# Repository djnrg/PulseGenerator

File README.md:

PulseGenerator
==============

Pulse Generator base on Arduino.

Change static voltage (max. 24V) to PWM. 

In this evolution we may setup frequency [1-500] and Duty Cycle [0-99].

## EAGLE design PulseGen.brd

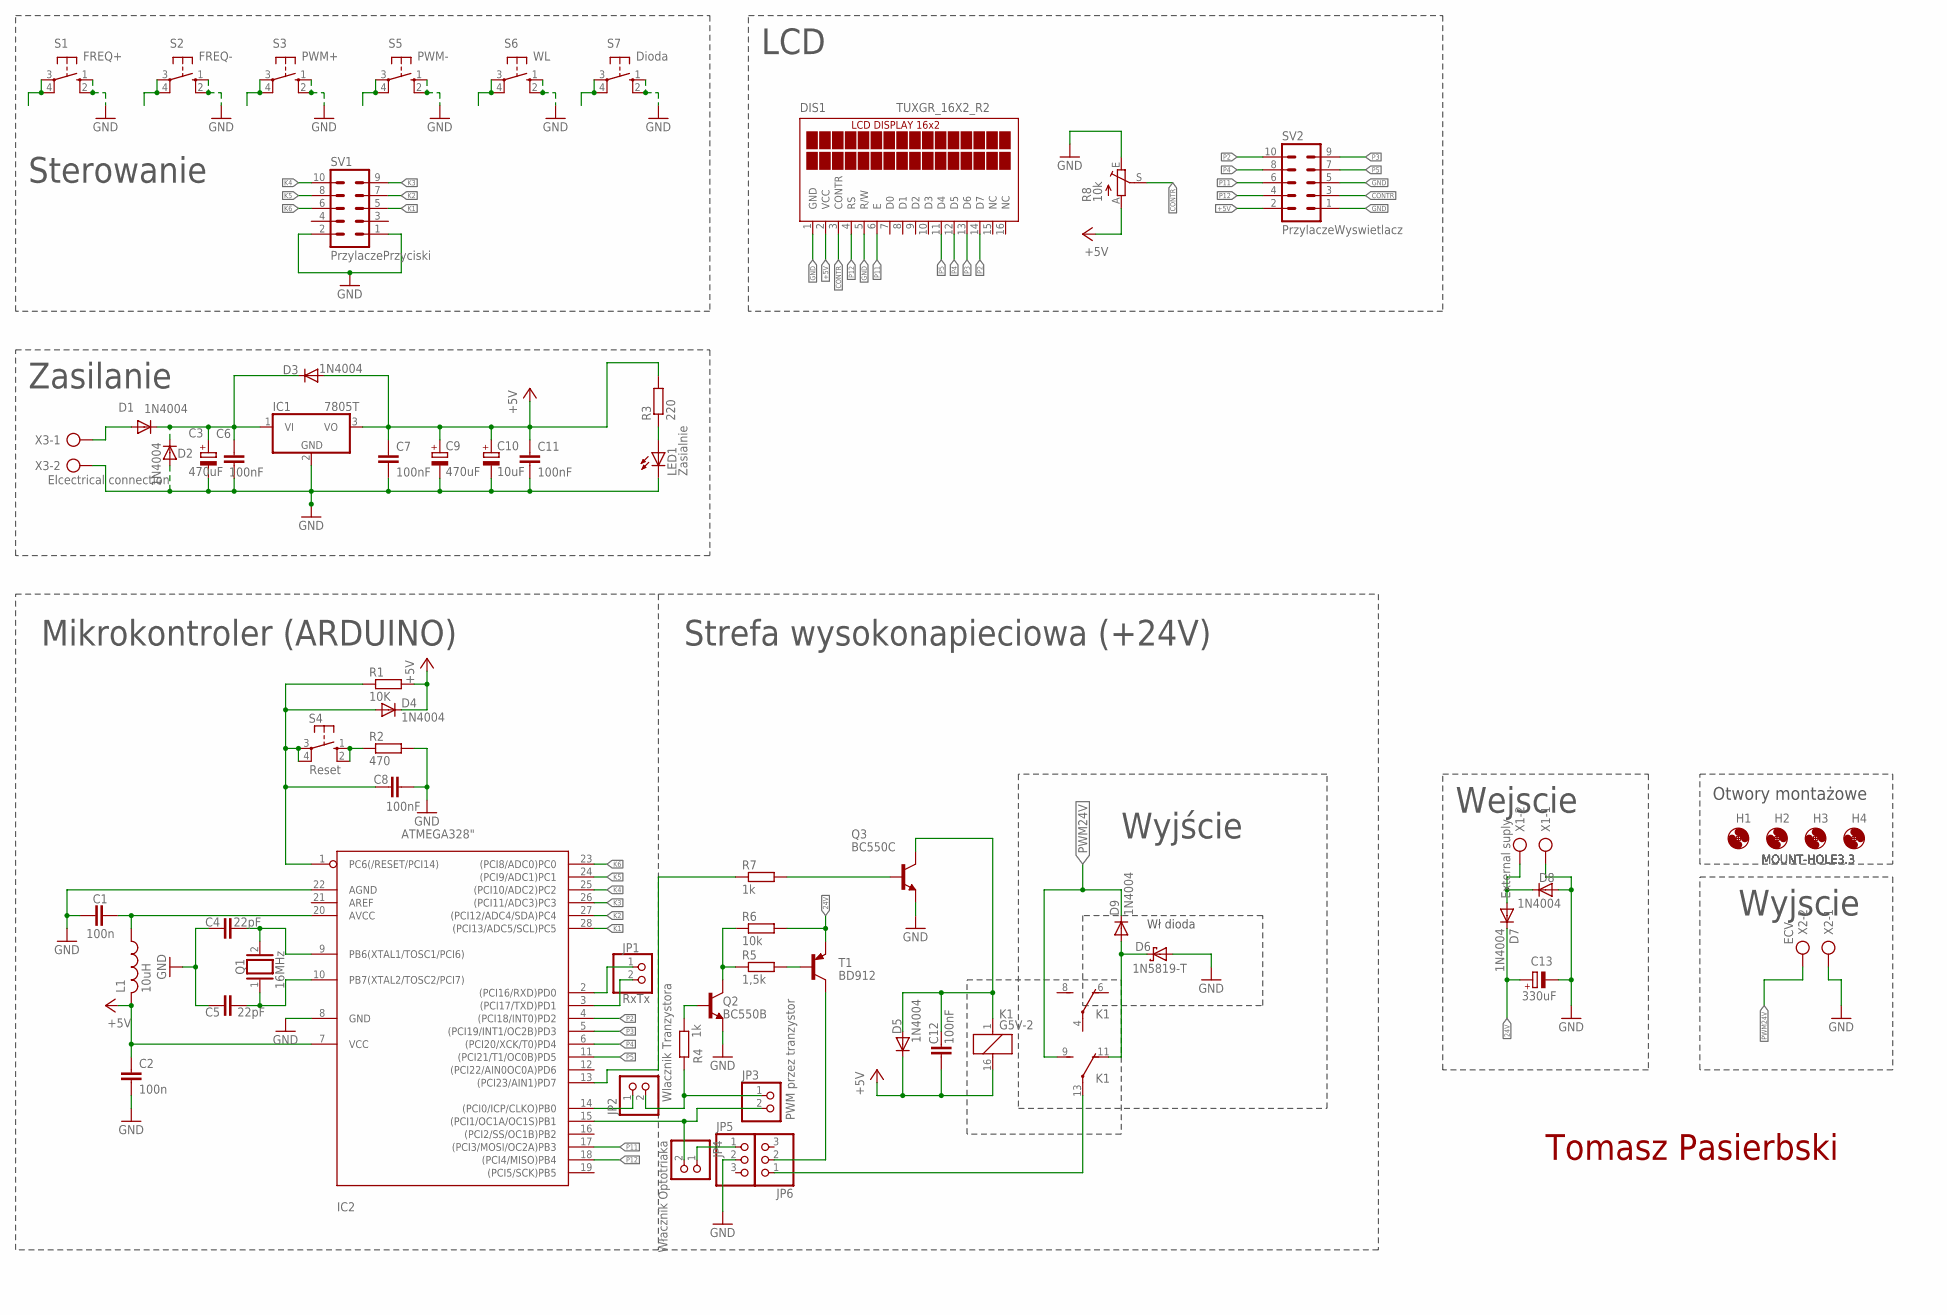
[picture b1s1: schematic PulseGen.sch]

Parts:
C1, C2: 100n; C025-030X050
C3, C9: 470uF; E3,5-8
C4, C5: 22pF; C025-024X044
C6, C7, C8, C11, C12: 100nF; C025-030X050
C10: 10uF; E5-6
C13: 330uF; E7,5-18
D1, D2, D3, D4, D5, D7, D8, D9: 1N4004; DO41-10
D6: 1N5819-T; DO41-7.6
DIS1: TUXGR_16X2_R2
H1, H2, H3, H4: MOUNT-HOLE3.3; 3,3
IC1: 7805T; TO220H
IC2: ATMEGA328"; ATMEGA328
JP1: RxTx; 1X02
JP2: Wlacznik Tranzystora; 1X02
JP3: PWM przez tranzystor; 1X02
JP4: Włacznik Optotriaka; 1X02
JP5, JP6: PINHD-1X3; 1X03
K1: G5V-2
L1: 10uH; 0204/7
LED1: Zasialnie; LED5MM
Q1: 16MHz; QS
Q2: BC550B; TO92-EBC
Q3: BC550C; TO92-EBC
R1: 10K; 0207/2V
R2: 470; 0207/2V
R3: 220; 0204/7
R4, R7: 1k; 0204/7
R5: 1,5k; 0207/12
R6: 10k; 0204/7
R8: 10k; CA6V
S1: FREQ+; B3F-10XX
S2: FREQ-; B3F-10XX
S3: PWM+; B3F-10XX
S4: Reset; B3F-10XX
S5: PWM-; B3F-10XX
S6: WL; B3F-10XX
S7: Dioda; B3F-10XX
SV1: PrzylaczePrzyciski; ML10
SV2: PrzylaczeWyswietlacz; ML10
T1: BD912; TO220
X1: External suply; AK300/2
X2: ECV; AK300/2
X3: Elcectrical connection; AK300/2

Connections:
24V: C13.+, D7.C, R6.2, T1.3 (E)
+5V: C2.1, C7.1, C9.+, C10.+, C11.1, C12.2, D3.A, D4.C, D5.C, DIS1.2 (VCC), IC1.3 (VO), IC2.7 (VCC), K1.16 (2), L1.2, R1.2, R3.2, R8.A, SV2.2
+24V: D7.A, D8.C, X1.2
CONTR: DIS1.3 (CONTR), R8.S, SV2.3
GND: C1.2, C2.2, C3.-, C4.1, C5.1, C6.2, C7.2, C8.2, C9.-, C10.-, C11.2, C13.-, D2.A, D6.A, D8.A, DIS1.1 (GND), DIS1.5 (R/W), IC1.2 (GND), IC2.8 (GND), IC2.22 (AGND), JP5.2, LED1.K (C), Q2.E, Q3.E, R2.2, R8.E, S1.1 (S), S1.2 (S1), S2.1 (S), S2.2 (S1), S3.1 (S), S3.2 (S1), S5.1 (S), S5.2 (S1), S6.1 (S), S6.2 (S1), S7.1 (S), S7.2 (S1), SV1.1, SV1.2, SV2.1, SV2.5, X1.1, X2.1, X3.2
K1: IC2.28 ((PCI13/ADC5/SCL)PC5), SV1.5
K2: IC2.27 ((PCI12/ADC4/SDA)PC4), SV1.7
K3: IC2.26 ((PCI11/ADC3)PC3), SV1.9
K4: IC2.25 ((PCI10/ADC2)PC2), SV1.10
K5: IC2.24 ((PCI9/ADC1)PC1), SV1.8
K6: IC2.23 ((PCI8/ADC0)PC0), SV1.6
unnamed: C5.2, IC2.10 (PB7(XTAL2/TOSC2/PCI7)), Q1.1
unnamed: C3.+, C6.1, D1.C, D2.C, D3.C, IC1.1 (VI)
unnamed: C4.2, IC2.9 (PB6(XTAL1/TOSC1/PCI6)), Q1.2
unnamed: D1.A, X3.1
unnamed: C12.1, D5.A, K1.1, Q3.C
unnamed: C1.1, IC2.20 (AVCC), L1.1
unnamed: Q3.B, R7.2
unnamed: JP2.2, JP3.1, R4.1
unnamed: Q2.C, R5.1, R6.1
unnamed: R2.1, S4.1 (S), S4.2 (S1)
unnamed: C8.1, D4.A, IC2.1 (PC6(/RESET/PCI14)), R1.1, S4.3, S4.4 (P1)
unnamed: JP6.1, K1.13
unnamed: IC2.13 ((PCI23/AIN1)PD7), R7.1
unnamed: Q2.B, R4.2
unnamed: R5.2, T1.1 (B)
unnamed: JP6.2, T1.2 (C)
unnamed: IC2.14 ((PCI0/ICP/CLKO)PB0), JP2.1
unnamed: LED1.A, R3.1
unnamed: IC2.15 ((PCI1/OC1A/OC1S)PB1), JP3.2, JP4.2
unnamed: S1.3, S1.4 (P1)
unnamed: S2.3, S2.4 (P1)
unnamed: S3.3, S3.4 (P1)
unnamed: S5.3, S5.4 (P1)
unnamed: S6.3, S6.4 (P1)
unnamed: S7.3, S7.4 (P1)
unnamed: IC2.3 ((PCI17/TXD)PD1), JP1.2
unnamed: IC2.2 ((PCI16/RXD)PD0), JP1.1
unnamed: JP4.1, JP5.1
unnamed: D6.C, D9.A, K1.11 (O)
P2: DIS1.14 (D7), IC2.4 ((PCI18/INT0)PD2), SV2.10
P3: DIS1.13 (D6), IC2.5 ((PCI19/INT1/OC2B)PD3), SV2.9
P4: DIS1.12 (D5), IC2.6 ((PCI20/XCK/T0)PD4), SV2.8
P5: DIS1.11 (D4), IC2.11 ((PCI21/T1/OC0B)PD5), SV2.7
P11: DIS1.6 (E), IC2.17 ((PCI3/MOSI/OC2A)PB3), SV2.6
P12: DIS1.4 (RS), IC2.18 ((PCI4/MISO)PB4), SV2.4
PWM24V: D9.C, K1.9 (S), X2.2

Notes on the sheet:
Zasilanie
LCD
Wejscie
Wyjscie
Sterowanie
Wł dioda
Wyjście
Mikrokontroler (ARDUINO)
Strefa wysokonapieciowa (+24V)
Otwory montażowe
Tomasz Pasierbski

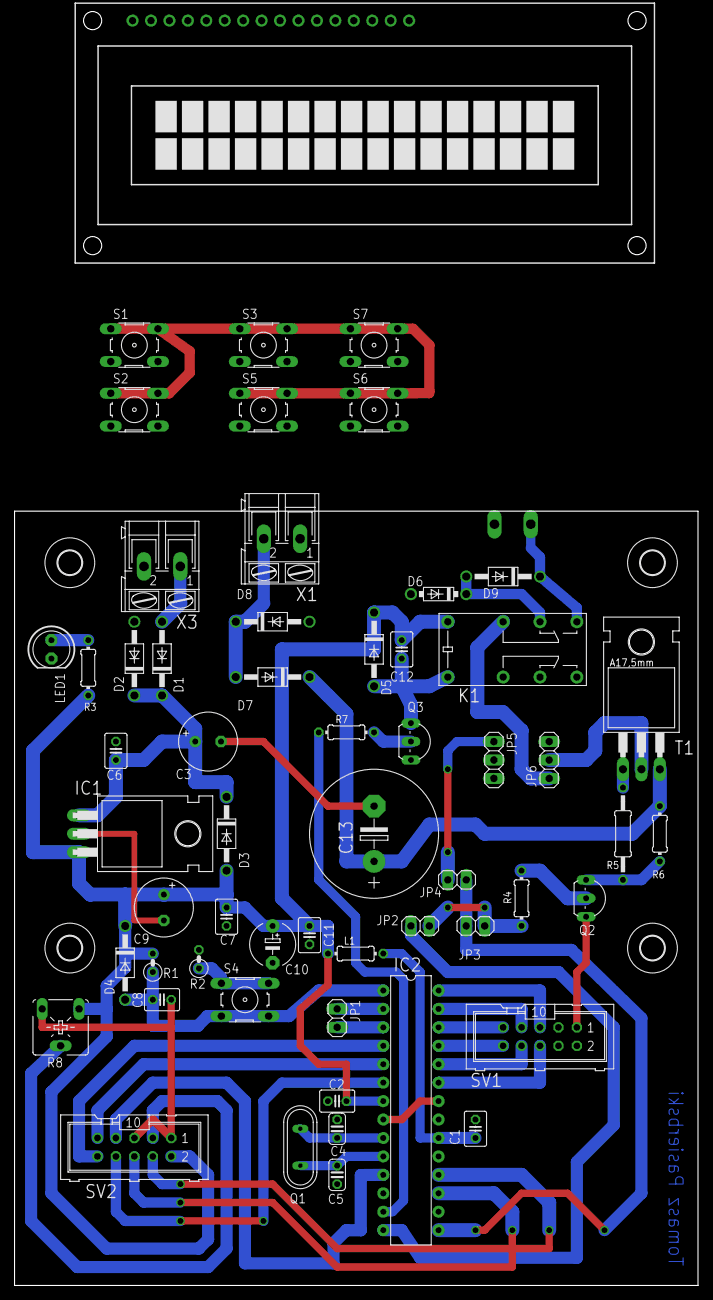
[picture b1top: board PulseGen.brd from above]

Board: 2 copper layers, 94.2 x 106.7 mm, 64 parts (1 on the bottom side), 47 nets.

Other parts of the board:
DRILEGEND: DRILEGEND
U$1: A4P-LOC

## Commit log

2014-03-03 PulsGen V0.98
    Preproduction version
2014-07-13 PulsGen 1.0.5
    Rozwiazanie problemu z zewnętrrznym sterowaniem.
